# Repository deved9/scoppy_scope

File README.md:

# scoppy scope

scoppy_scope is a project of mine, where i try to fit a custom small form-factor 2 channel osciloscope to a Thinkpad T430's smart card reader bay.

Project is currently in development, the frontend is tested to be fully working without the use of the range switching IC. 

This project was inspired by the [Scoppy oscilloscope and logic analyzer project](https://github.com/fhdm-dev/scoppy) which sadly only supports Android devices as of this date. 

The digital part of the project, including part of the schematic and footprints, has been taken from the [Adafruit QT Py RP2040](https://github.com/adafruit/Adafruit-QT-Py-RP2040-PCB)

As of right now, the PCB is close to finished. The main focus will be shifted to the software side of the project.

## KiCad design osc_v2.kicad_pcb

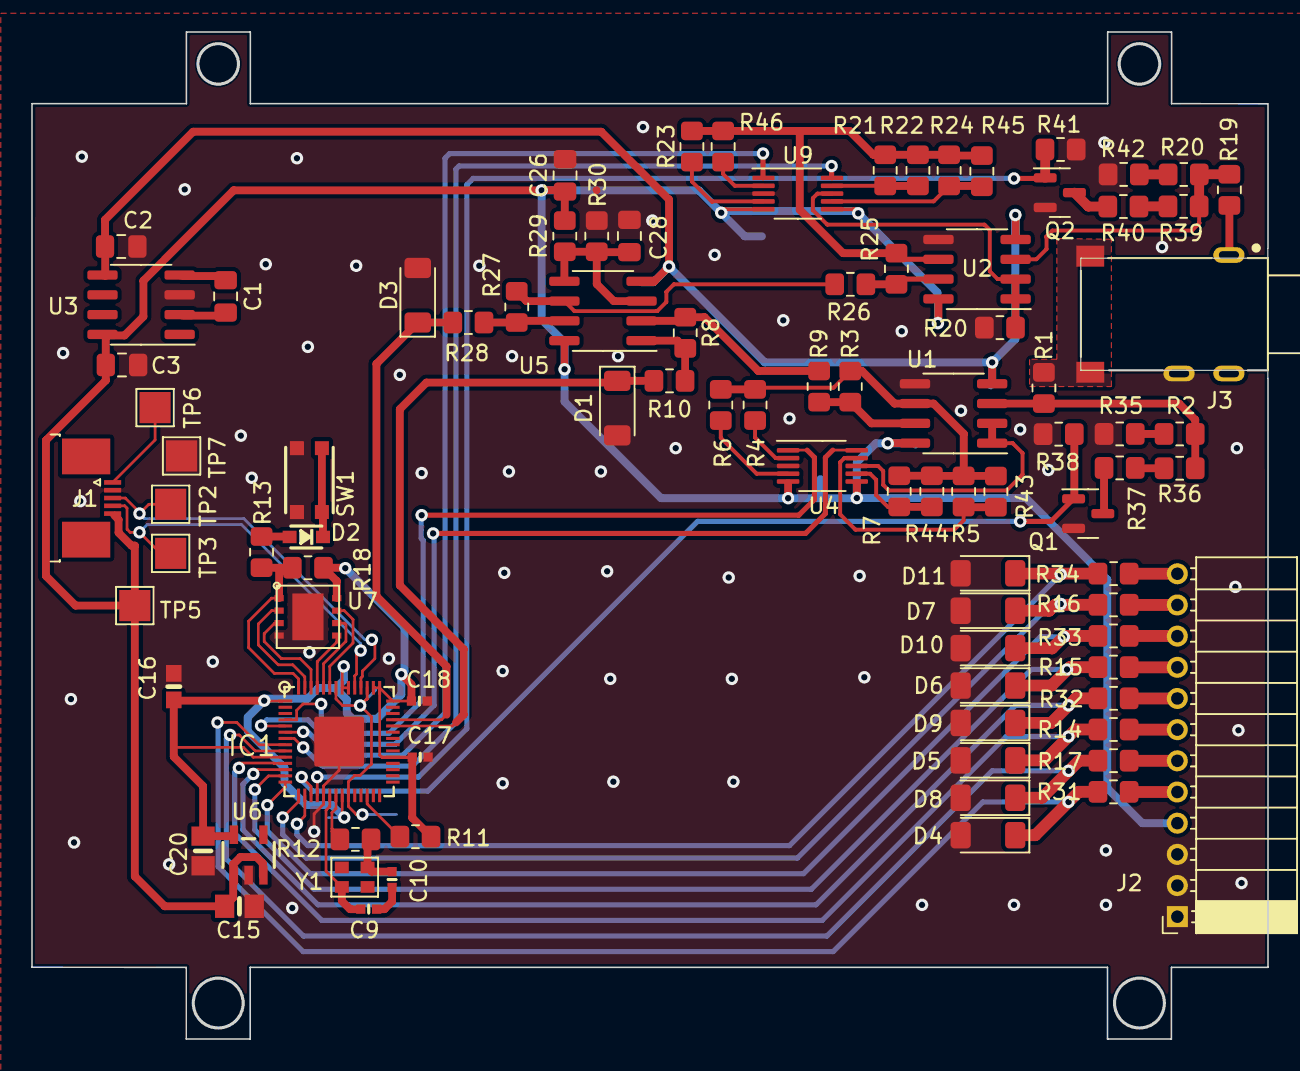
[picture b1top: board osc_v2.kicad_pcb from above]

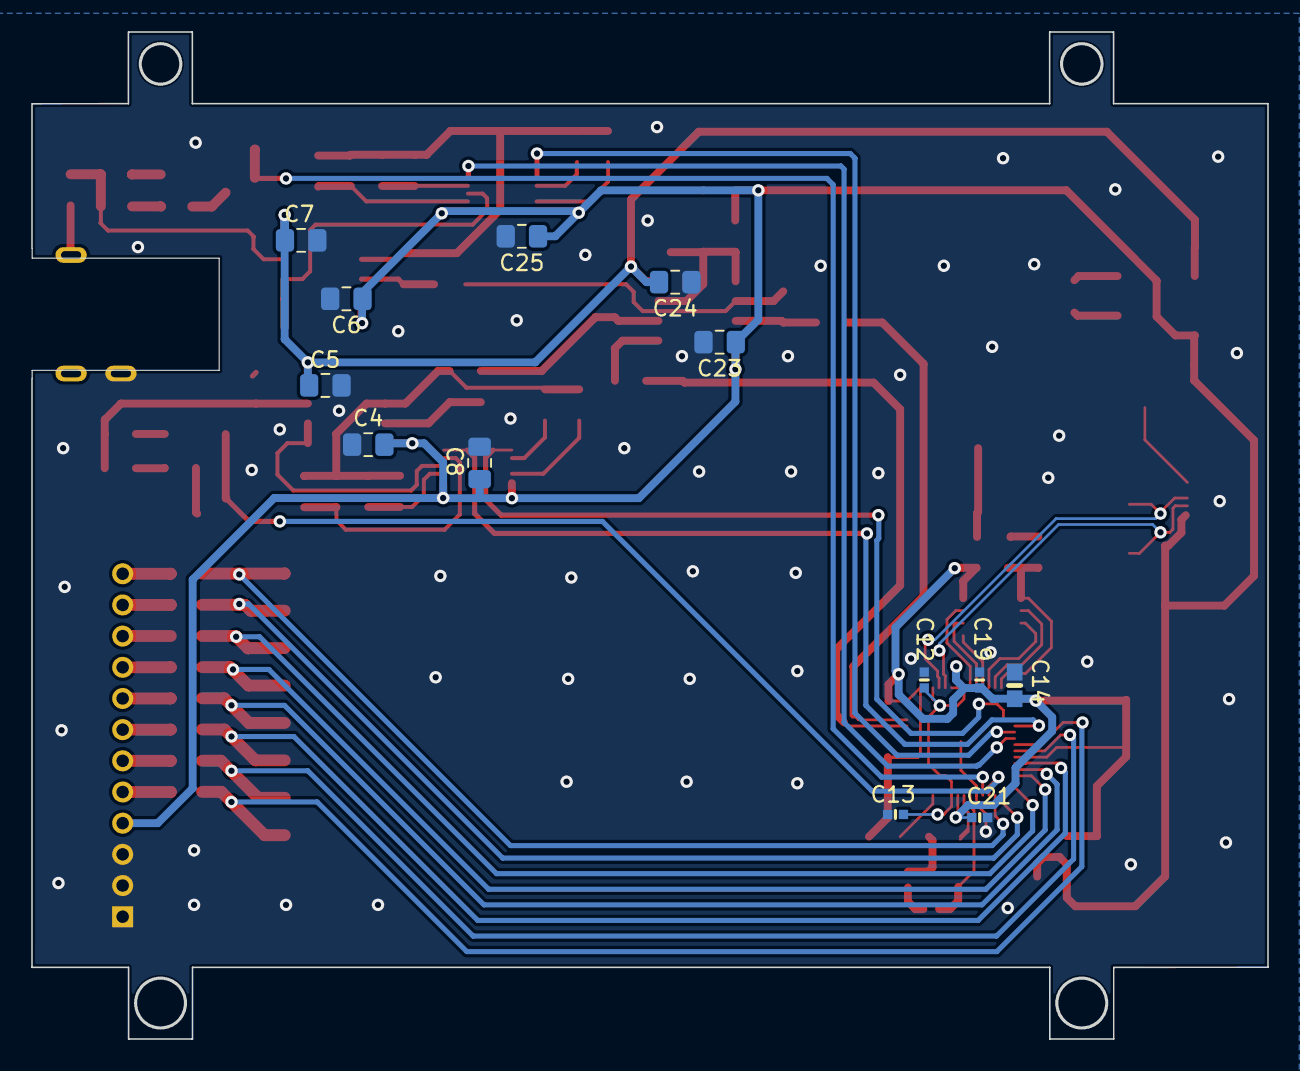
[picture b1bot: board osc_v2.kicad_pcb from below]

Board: 2 copper layers, 79.2 x 64.5 mm, 104 parts (13 on the bottom side), 76 nets.

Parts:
C1: 10u; C_0805_2012Metric_Pad1.18x1.45mm_HandSolder
C2, C3, C4, C5, C6, C7, C8, C23, C24, C25, C26, C28: 100u; C_0805_2012Metric_Pad1.18x1.45mm_HandSolder
C9, C10: 22pF; _0402NO
C12, C13, C17, C18, C19, C21: 0.1uF; _0402NO
C14, C16: 1uF; 0603-NO
C15, C20: 10uF; 0805-NO
D1, D3, D4, D5, D6, D7, D8, D9, D10, D11: BZV55B3V3; D_MiniMELF
D2: NSR0320; SOD-323_MINI
IC1: RP2040_QFN56; QFN56_7MM_REDUCEDEPAD
J1: Conn_01x05; TE_0-1734839-5_1x05-1MP_P0.5mm_Horizontal
J2: Conn_01x12; PinSocket_1x12_P2.00mm_Horizontal
J3: SJ-3501-SMT; CUI_SJ-3501-SMT
Q1, Q2: BSN20; SOT-23
R1, R19: 1M; R_0805_2012Metric_Pad1.20x1.40mm_HandSolder
R2, R3, R8, R9, R20, R25, R26, R27, R35, R42: 100k; R_0805_2012Metric_Pad1.20x1.40mm_HandSolder
R4, R36, R39, R46: 1k; R_0805_2012Metric_Pad1.20x1.40mm_HandSolder
R5, R21: 5k6; R_0805_2012Metric_Pad1.20x1.40mm_HandSolder
R6, R23: 10k; R_0805_2012Metric_Pad1.20x1.40mm_HandSolder
R7, R24: 56k; R_0805_2012Metric_Pad1.20x1.40mm_HandSolder
R10, R14, R15, R16, R17, R28, R31, R32, R33, R34: 100R; R_0805_2012Metric_Pad1.20x1.40mm_HandSolder
R11, R18: 10K; R_0805_2012Metric_Pad1.20x1.40mm_HandSolder
R12, R13: 1K; R_0805_2012Metric_Pad1.20x1.40mm_HandSolder
R20#2: 197k; R_0805_2012Metric_Pad1.20x1.40mm_HandSolder
R22, R43: 47k; R_0805_2012Metric_Pad1.20x1.40mm_HandSolder
R29: 9k1; R_0805_2012Metric_Pad1.20x1.40mm_HandSolder
R30: 1k8; R_0805_2012Metric_Pad1.20x1.40mm_HandSolder
R37, R40: 680R; R_0805_2012Metric_Pad1.20x1.40mm_HandSolder
R38, R41: 330R; R_0805_2012Metric_Pad1.20x1.40mm_HandSolder
R44, R45: 470k; R_0805_2012Metric_Pad1.20x1.40mm_HandSolder
SW1: KMR2; BTN_KMR2_4.6X2.8
TP2: D-; TestPoint_Pad_2.0x2.0mm
TP3: D+; TestPoint_Pad_2.0x2.0mm
TP5: 5V; TestPoint_Pad_2.0x2.0mm
TP6: SC_DETECT; TestPoint_Pad_2.0x2.0mm
TP7: GND; TestPoint_Pad_2.0x2.0mm
U1, U2, U5: LM358; SOIC-8_3.9x4.9mm_P1.27mm
U3: ICL7660; SOIC-8_3.9x4.9mm_P1.27mm
U4, U9: VSSOP-10_3x3mm_P0.5mm
U6: AP2112K-3.3; SOT23-5
U7: 8MB QSPI Flash; USON8_4X4
Y1: 12MHZ; CRYSTAL_2.5X2

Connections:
1.2V: C12.2, C13.2, IC1.23 (DVDD), IC1.45 (VREG_VOUT), IC1.50 (DVDD)
+3V3: C14.1, C16.1, C17.1, C18.1, C19.1, C20.1, C21.1, IC1.1 (IOVDD), IC1.10 (IOVDD), IC1.22 (IOVDD), IC1.33 (IOVDD), IC1.42 (IOVDD), IC1.43 (ADC_IOVDD), IC1.44 (VREG_IOVDD), IC1.48 (USB_IOVDD), IC1.49 (IOVDD), R11.1, R18.2, U6.5 (OUT), U7.8 (VCC)
+5V: C3.1, C4.1, C6.1, C8.2, C15.1, C23.1, C25.2, C26.1, J1.5, J2.4, R29.1, TP5.1, U1.8 (V+), U2.8 (V+), U3.8 (V+), U4.5 (EN), U4.6 (VCC), U5.8 (V+), U6.1 (IN), U6.3 (EN), U9.5 (EN), U9.6 (VCC)
-5V: C2.1, C5.2, C7.2, C24.2, U1.4 (V-), U2.4 (V-), U3.5 (VOUT), U5.4 (V-)
/RP2040/D+: IC1.47 (USB_D+), J1.4, TP3.1
/RP2040/D-: IC1.46 (USB_D-), J1.3, TP2.1
/RP2040/QSPI_CS: IC1.56 (~QSPI_CS), R13.1, R18.1, U7.1 (SSEL)
/RP2040/QSPI_DATA[0]: IC1.53 (QSPI_SD0), U7.5 (MOSI)
/RP2040/QSPI_DATA[1]: IC1.55 (QSPI_SD1), U7.2 (MISO)
/RP2040/QSPI_DATA[2]: IC1.54 (QSPI_SD2), U7.3 (WP#/IO2)
/RP2040/QSPI_DATA[3]: IC1.51 (QSPI_SD3), U7.7 (HOLD#/IO3)
/RP2040/QSPI_SCK: IC1.52 (QSPI_SCLK), U7.6 (SCK)
/RP2040/~RESET: IC1.26 (/RUN), R11.2
CH1: D1.1 (K), IC1.38 (GPIO26/AD0), R10.2
CH1_RANGE0: IC1.4 (GPIO2), U4.1 (A0)
CH1_RANGE1: IC1.5 (GPIO3), U4.10 (A1)
CH1_RANGE2: IC1.17 (GPIO14), Q1.1 (G), R38.1
CH1_RAW: J3.2, J3.4, R1.1
CH2: D3.1 (K), IC1.39 (GPIO27/AD1), R28.2
CH2_RANGE0: IC1.6 (GPIO4), U9.1 (A0)
CH2_RANGE1: IC1.7 (GPIO5), U9.10 (A1)
CH2_RANGE2: IC1.18 (GPIO15), Q2.1 (G), R41.1
CH2_RAW: J3.1, J3.5, R19.1
DC_OFFSET: C28.1, R29.2, R30.2, U5.3 (+), U5.5 (+)
GND: C2.2, C3.2, C4.2, C5.1, C6.2, C7.1, C8.1, C12.1, C13.1, C14.2, C15.2, C16.2, C17.2, C18.2, C19.2, C20.2, C21.2, C23.2, C24.1, C25.1, C26.2, C28.2, D1.2 (A), D3.2 (A), D4.2 (A), D5.2 (A), D6.2 (A), D7.2 (A), D8.2 (A), D9.2 (A), D10.2 (A), D11.2 (A), IC1.19 (TESTEN), IC1.P$1 (GND), J1.2, J2.1, J2.2, J2.3, J3.3, Q1.2 (S), Q2.2 (S), R20#2.2, R30.1, R35.2, R38.2, R41.2, R42.2, SW1.B (S), SW1.B' (S1), TP7.1, U1.5 (+), U2.5 (+), U3.3 (GND), U4.3 (GND), U6.2 (GND), U7.4 (VSS), U7.PAD (VSS), U9.3 (GND)
LA0: D4.1 (K), IC1.8 (GPIO6), R31.2
LA0_I: J2.5, R31.1
LA1: D8.1 (K), IC1.9 (GPIO7), R17.2
LA1_I: J2.6, R17.1
LA2: D5.1 (K), IC1.11 (GPIO8), R14.2
LA2_I: J2.7, R14.1
LA3: D9.1 (K), IC1.12 (GPIO9), R32.2
LA3_I: J2.8, R32.1
LA4: D6.1 (K), IC1.13 (GPIO10), R15.2
LA4_I: J2.9, R15.1
LA5: D10.1 (K), IC1.14 (GPIO11), R33.2
LA5_I: J2.10, R33.1
LA6: D7.1 (K), IC1.15 (GPIO12), R16.2
LA6_I: J2.11, R16.1
LA7: D11.1 (K), IC1.16 (GPIO13), R34.2
LA7_I: J2.12, R34.1
unnamed: C9.1, C10.1
unnamed: C10.2, R12.1, Y1.1
unnamed: D2.A, R13.2
unnamed: C9.2, IC1.20 (XIN), Y1.3 (2)
unnamed: IC1.21 (XOUT), R12.2
unnamed: J1.1, TP6.1
unnamed: Q1.3 (D), R37.2
unnamed: Q2.3 (D), R40.2
unnamed: R2.2, R35.1
unnamed: R3.2, R9.1, U1.7
unnamed: R8.2, R10.1, U5.1
unnamed: R20.2, R42.1
unnamed: R25.2, R26.1, U2.7
unnamed: R27.2, R28.1, U5.7
unnamed: R36.2, R37.1
unnamed: R39.2, R40.1
unnamed: D2.C, SW1.A, SW1.A' (P1)
unnamed: R1.2, R2.1, R36.1, U1.3 (+)
unnamed: U1.1, U1.2 (-), U4.8 (D1)
unnamed: R3.1, R4.2, R5.2, R6.2, R7.2, R43.2, R44.2, U1.6 (-)
unnamed: R19.2, R20.1, R39.1, U2.3 (+)
unnamed: R20#2.1, U2.1, U2.2 (-), U9.8 (D1)
unnamed: R21.2, R22.2, R23.2, R24.2, R25.1, R45.2, R46.2, U2.6 (-)
unnamed: C1.1, U3.2 (CAP+)
unnamed: C1.2, U3.4 (CAP-)
unnamed: R4.1, U4.2 (S1)
unnamed: R5.1, R43.1, U4.9 (S2)
unnamed: R6.1, U4.4 (S3)
unnamed: R7.1, R44.1, U4.7 (S4)
unnamed: R8.1, R9.2, U5.2 (-)
unnamed: R26.2, R27.1, U5.6 (-)
unnamed: R46.1, U9.2 (S1)
unnamed: R21.1, R22.1, U9.9 (S2)
unnamed: R23.1, U9.4 (S3)
unnamed: R24.1, R45.1, U9.7 (S4)
